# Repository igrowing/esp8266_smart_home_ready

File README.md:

# ESP8266 based Smart Home System
## Principle
### Types of smart home
- Centralized - there is one smart hub in the house and bunch of perfieral devices just perform its commands.
- Decentralized - every edge device is smart and self-contained.
- Cloud - the same as centralized, just the hub is not in your house... with all pros and cons.
- Hybrid - every edge device is smart enough to perform on its own, plus it communicates with the hub in your house or in cloud when/if needed.

We develop the **Hybrid Smart Home**, as the most resilient, safe, and serviceable system.

### What is Smart?

Today every relay connected to Bluetooth called "smart". De facto, this type of "smart" is actually "controlled" device. It is controlled by humans via phone/app/cloud/vocal assistant. So human is smart in this case, not the device.

Smart home consists devices (edge peripherals, hub(s), and cloud connection) which are able to learn habitants behavior, preferences, rules, and perform accordingly to them automatically.

**Smart home must serve people**, not people should care about smart home.

The main concept of our smart home is:
### Home must serve you. You should enjoy ###

This is what this project about.

## Active parts
- [Room sensor](https://github.com/igrowing/esp8266_smart_home_ready/tree/master/modules/room_sensor) based on ESP-easy.
- [Room sensor](https://github.com/igrowing/esp8266_smart_home_ready/tree/master/modules/room%20sensor%20v2) based on Homie IoT.
- [Leakage detector, door/window sensor, remote bell button, etc.](https://github.com/igrowing/esp8266_smart_home_ready/tree/master/modules/leakage_detector) based on ESP-easy.
- [Remote light switch](https://github.com/igrowing/esp8266_smart_home_ready/tree/master/modules/remote%20light%20switch) based on Homie IoT.
- [Sewage pump controller](https://github.com/igrowing/esp8266_smart_home_ready/tree/master/modules/sewage%20pump%20controller) based on Homie IoT.
- [Garden sensor](https://github.com/igrowing/esp8266_smart_home_ready/tree/master/modules/garden_sensor) based on ESP-easy.
- [Water monitor and valve, Schieber](https://github.com/igrowing/esp8266_smart_home_ready/tree/master/modules/schieber) based on Homie IoT.
- [Boilero: the really smart boiler](https://github.com/igrowing/esp8266_smart_home_ready/tree/master/modules/boilero) based on Homie IoT.

## Abandoned part

Spanish proverb says: "Wise man changes his mind, a fool never".
We admit that struggling over the same problems as other developers is not effective way for progress.
Therefore we picked 2 the most usable frameworks (EspEasy and Homie) to implement ESP8266 based part of the smart home.

This impacts a little the fully autonomous OTA idea.
However, this allows us to move faster to end-to-end solution.

## The goal
Make fully automated OTA for ESP8266 under NodeMCU.

The software upload and update to the ESP8266 is trivial via UART. This way is not applicable for mass-deployed modules.

There are geek-driven solutions for OTA: the human (engineer or skilled person) should initiate file upload one-by-one to every particular module. This is not applicable too: the human is unable to do that for hundreds and thousands of modules, tens of files per module.

Therefore, module should initiate itself on the server (register) and request updates on periodic basis. Once developer releases the update to the server, every single ESP8266 module should update itself asynchronously.

### Implementation
**ESP8266 side:** Lua files to be uploaded to the module during "manufacturing" process.

**Server side:** The server files to be installed (copied) to the local server during initial installation process.

## Initial configuration and use
On the server run `smart-home-server.py file_repository`.

The ESP8266 module once powered up will run as AP (access point named SHMxxxxxx, where x-es stand for ID number of the module). Connect ot the module via any browser to address 192.168.4.1. Fill mandatory (and optional if needed) fields. Click Save button. That's it.

The ESP8266 module will restart and connect the server looking for the update. Once new files placed into the file repository the module will download them and run the code.

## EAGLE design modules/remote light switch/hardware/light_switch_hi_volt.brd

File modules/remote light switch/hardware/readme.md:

Schematics in both Eagle SCH and PDF formats.
Board in Eagle BRD format.

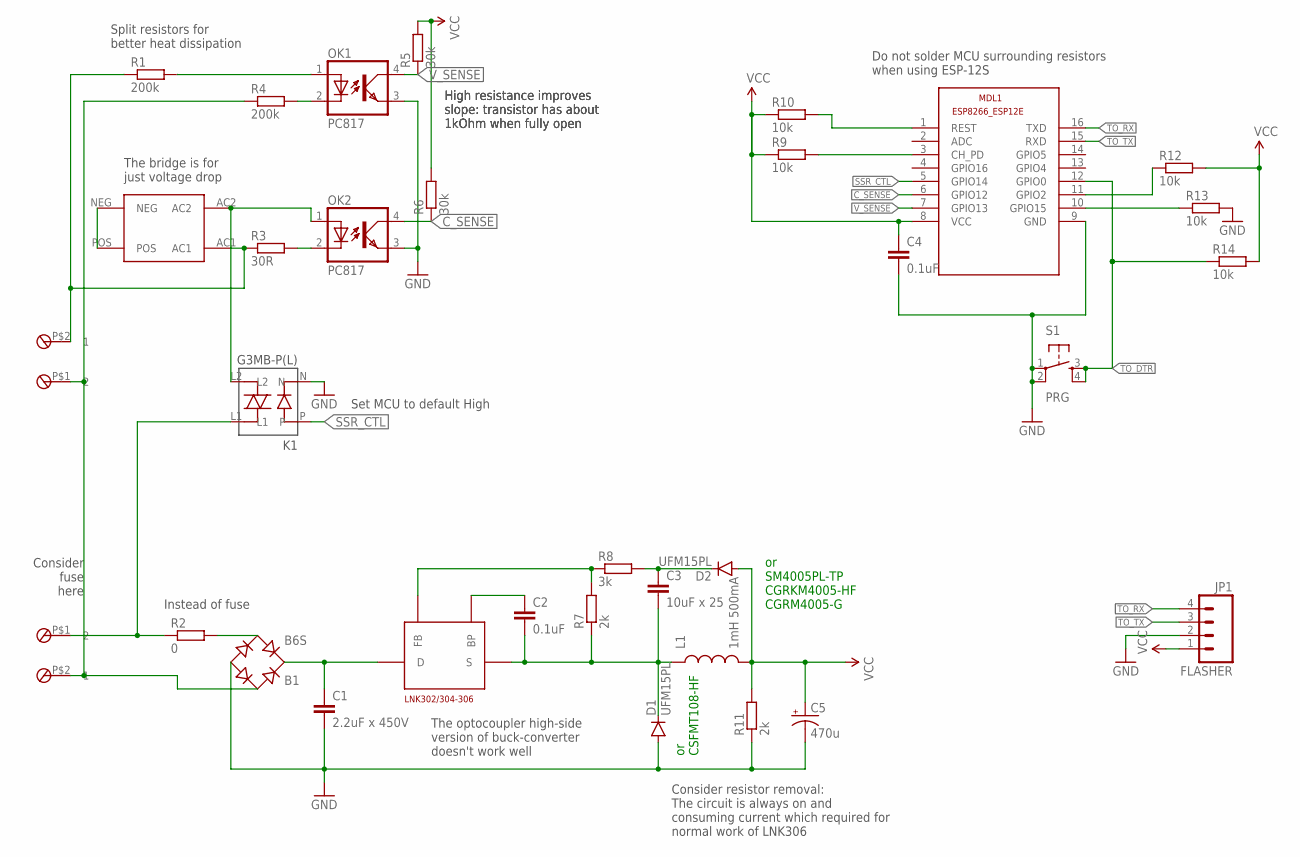
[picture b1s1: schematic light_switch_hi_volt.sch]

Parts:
B1: B6S; MBS
C1: 2.2uF x 450V; C2220K; MPN CKG57NX7T2W225M500JH
C2, C4: 0.1uF; 0805; MPN TMK107BJ104KA-T
C3: 10uF x 25; 0805; MPN GRM219R61E106KA12D
C5: 470u; EIA7343
D1, D2: UFM15PL; SOD-123; MPN UFM15PL-TP
J1, J2: 2POS_TERM_BLK_10A_3.5MM
JP1: FLASHER; 1X04
K1: G3MB-P(L); GB3M_SSR
L1: 1mH 500mA; CDRH125; MPN 46105C
MDL1: ESP8266-12EESP8266-ESP12E; ESP8266-ESP12E
OK1, OK2: PC817; SMD4
R1, R4: 200k; R0805; MPN CRCW06032K00FKEA
R2: 0; R0603; MPN CRCW06032K00FKEA
R3: 30R; R0603; MPN CRCW06032K00FKEA
R5, R6: 30k; R0603; MPN CRCW06032K00FKEA
R7, R11: 2k; R0603; MPN CRCW06032K00FKEA
R8: 3k; R0603; MPN CRCW06032K00FKEA
R9, R10, R12, R13, R14: 10k; R0603
S1: PRG; TACTILE-SWITCH-SMD
U1: Z4DGP406L-HF
U2: LNK306; SO08

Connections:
C_SENSE: MDL1.6 (GPIO12), OK2.4 (COL), R6.1
GND: B1.-, C1.2, C4.2, C5.C (-), D1.A, JP1.2, K1.N, MDL1.9 (GND), OK1.3 (EMIT), OK2.3 (EMIT), R11.1, R13.2, S1.1, S1.2
IO2: MDL1.11 (GPIO2), R12.1
IO15: MDL1.10 (GPIO15), R13.1
unnamed: B1.+, C1.1, U2.4 (D)
unnamed: J2.P$1 (2), K1.L1, R2.1
unnamed: OK1.1 (A), R1.2
unnamed: B1.AC1, J1.P$1 (2), J2.P$2 (1), R4.1
unnamed: U1.NEG, U1.POS
unnamed: B1.AC2, R2.2
unnamed: K1.L2, OK2.1 (A), U1.AC2
unnamed: J1.P$2 (1), R1.1, R3.1, U1.AC1
unnamed: OK2.2 (C), R3.2
unnamed: OK1.2 (C), R4.2
unnamed: MDL1.3 (CH_PD), R9.2
unnamed: C2.1, U2.1 (BP)
unnamed: C2.2, C3.2, D1.C, L1.1, R7.1, U2.5 (S), U2.6 (S), U2.7 (S), U2.8 (S)
unnamed: R7.2, R8.1, U2.2 (FB)
unnamed: C3.1, D2.C, R8.2
SSR_CTL: K1.P, MDL1.5 (GPIO14)
TO_DTR: MDL1.12 (GPIO0), R14.1, S1.3, S1.4
TO_RTS: MDL1.1 (REST), R10.2
TO_RX: JP1.4, MDL1.16 (TXD)
TO_TX: JP1.3, MDL1.15 (RXD)
VCC: C4.1, C5.A (+), D2.A, JP1.1, L1.2, MDL1.8 (VCC), R5.2, R6.2, R9.1, R10.1, R11.2, R12.2, R14.2
V_SENSE: MDL1.7 (GPIO13), OK1.4 (COL), R5.1

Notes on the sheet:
or CSFMT108-HF
or SM4005PL-TP CGRKM4005-HF CGRM4005-G
Split resistors for better heat dissipation
High resistance improves slope: transistor has about 1kOhm when fully open
The bridge is for just voltage drop
Consider resistor removal: The circuit is always on and consuming current which required for normal work of LNK306
The optocoupler high-side version of buck-converter doesn't work well
Instead of fuse
Do not solder MCU surrounding resistors when using ESP-12S
Set MCU to default High
Consider fuse here

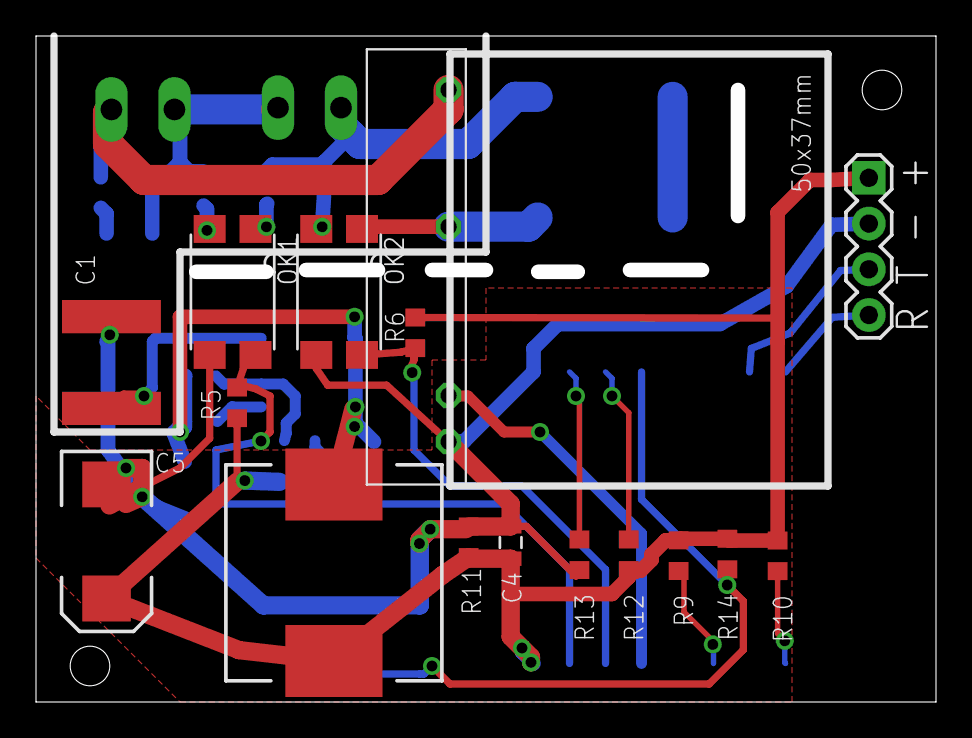
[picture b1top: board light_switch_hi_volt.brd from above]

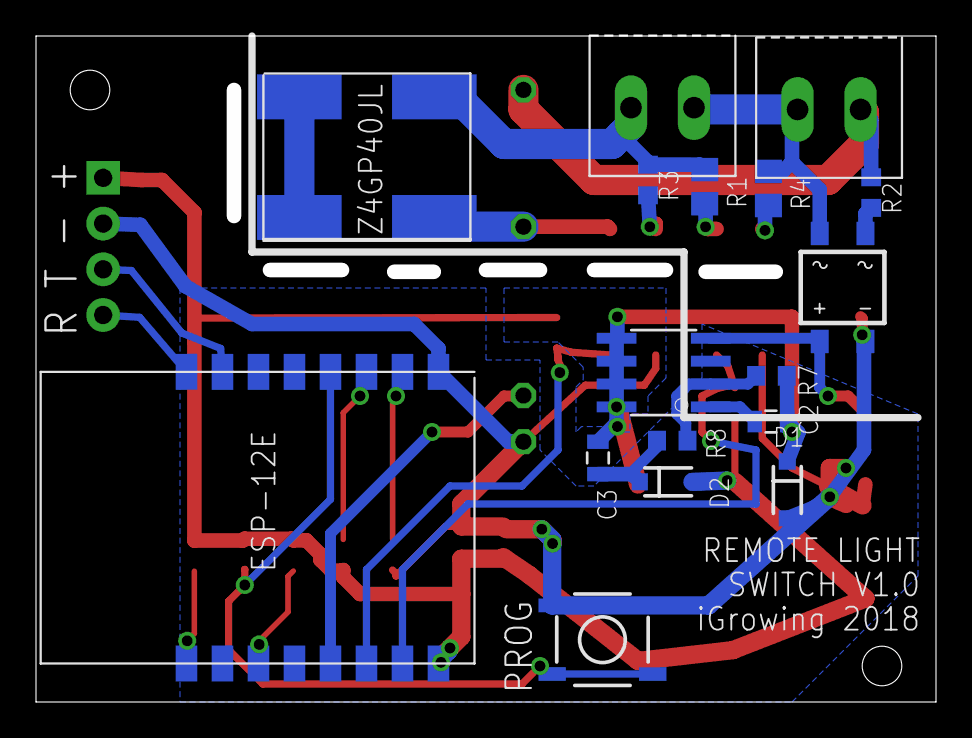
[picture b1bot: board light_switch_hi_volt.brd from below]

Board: 2 copper layers, 49.2 x 36.2 mm, 33 parts (17 on the bottom side), 26 nets.

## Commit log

2018-03-25 Create readme.md
    Initial commit
2018-03-25 Update readme.md
    alternatives added
2018-03-25 Update readme.md
    todos
2018-03-31 Schematics and rules
2018-03-31 Instructions added
2018-03-31 init.rev
2018-03-31 Config.dat added
2018-03-31 instructions improved.
2018-03-31 Instructions added.
2018-03-31 Project content added
2018-07-16 BME680 recommended
2018-07-16 init.rev.
2018-07-16 formatting
2018-07-16 uploaded files.
2018-11-02 Files added.
2018-11-02 ini file
2018-11-02 Create placeholder
2018-11-02 the sketch
2018-11-04 Noise immunity
2018-11-04 Keep/restore last state, Noise immunity
2018-11-04 Description
2018-12-08 ini files added
2018-12-08 typos
2018-12-16 Schematics
2018-12-16 Init.publish.
2018-12-16 LAF improved
2018-12-16 Node-RED flow for UI of the pump controller
2018-12-16 pictures
2018-12-16 pictures added
2018-12-16 Rename nr_flow.js to nr_flow.json
2018-12-19 install mode added
2018-12-19 Improved current/distance measure, alerting, install mode added.
2018-12-19 Improved stability and protection.
2018-12-28 Allow scheduler on/off via MQTT
    New event added due to inability of EspEasy to use taskvalueset command directly from MQTT
2018-12-28 Fix NTP server reference
2018-12-28 Usage added.
2019-01-19 Complete leakage procedure with deepsleep
    Powering off the unit on leakage doesn't work. The unit awakes up immediately. Deepsleep makes awake slow. Power cycle the unit to exit the deepsleep cycle.
2019-01-19 Usage added
2019-02-16 Debugged distance meter
2019-02-16 Pictures seen now.
2019-03-11 Adapted for compilation for 4MB flash
2019-03-11 Bugfix: avoid false alerts about relay state
2019-03-11 STL box model for 3D printer
2019-03-22 Don't retain MQTT messages
2019-03-22 Improved controller online/offline detection
2019-03-22 Node-RED flow example added
2019-03-31 Added air quality calculation and reporting
2019-04-04 Added verbal weather forecast reporting
2019-04-04 Node-Red integration example
2019-04-04 Node-Red flow example
2019-04-05 UI screenshot added
2019-04-05 Bug fix in weather forecast. Reorg write to file
2019-04-21 Improve report consistency
2019-07-07 Init. rev.
2019-07-07 Wave added
2019-07-08 performance optimized
2019-07-21 Added usage by MQTT
2019-07-21 How it works added
2019-07-24 Optimized and visually reorg'd
2019-07-24 picture added
2019-07-26 Optimized Flash use and water reporting
2019-07-27 Node-Red flow picture added
2019-07-27 Typo
2019-07-27 Added extrapolation of water flow while Shiber is booting and water isn't counted
2019-07-30 update flow
2019-07-30 Node-Red flow added
2019-08-02 Added periodic report of distance threshold to keep UI updated
2019-08-02 Remove duplicated invocation of 15sec power_timer. Optimization.
2019-08-02 Mount added
2019-08-05 UI usage added
2019-08-09 Hall to Reed upgrade
2019-08-09 Bugfix: report measurement only after all settings restored from Flash
2019-08-11 Added data load to InfluxDB
2019-08-15 Adjust volume calculation by flow speed
2019-08-23 Optimize variable reporting and water flow calculation
2019-08-24 log() -> log10f()
2019-09-11 Optimizations, bugfixes, reorg
2019-09-13 Stuff added
2019-09-14 Minor bugfix
2019-09-17 Avoid flow alerting before flow counters initialized
2020-02-14 Improved EMI, reorg.
2020-02-14 Remove diode to get reliable water reading
2020-02-14 Enable debug
2020-02-16 Soft_delay() instead of delay(). Fix get_liters(). Power off is no wifi in timeout.
2020-03-13 Replace mistaken commit
2020-03-14 schematics added
2020-03-18 Refactoring and bug fixes
2020-03-18 EMI + better PSU
2020-03-20 Make all settings as properties, add feedback to UI
2020-03-20 Replace dedicated PSU with generic USB PSU + LDO
2020-03-20 More docs and pictures
2020-03-20 attempt to fix image size
2020-03-20 Fix picture resizing
2020-03-20 Minor fix
2020-03-23 Logic explained
2020-04-24 Improve calibration in volume calc
2021-01-15 Air pressure correction described
2021-01-16 Added correction with dependency of air pressure
2021-01-16 ini-file added
2021-01-16 platformio.ini update
2021-01-16 Bug fixes
2021-01-23 Bug fix and better corrected time report
2021-02-02 Workaround bug in Ticker library
2021-02-08 Tuning to pressure compensation mechanism.
2021-02-19 readme.md update
2021-03-05 Create temp
2021-03-05 Pictures upload
2021-03-05 Code upload
2021-03-05 readme upload
2021-03-06 More pictures added
2021-03-06 Bug fix in water level representation
2021-03-06 remove it
2021-04-02 2 more buttons added to Web-UI
2021-04-02 Add alert for long no drink timeout
2021-04-02 Readme update
2021-04-17 Improved messaging, Filter hours bug fix
2021-08-06 Bug fix: restart the pet scanning if the pet was thirsty
2021-08-16 Fix link
2021-08-16 Warning!
2022-12-23 Update to work with Maxbotix MB-7062 sonar
2022-12-24 Turn off the sonar while not measuring.
2023-02-16 put placeholder
2023-02-16 Works
2023-02-17 Schematics added.
2023-02-18 Bug fix.
2023-04-19 Set explisit version of espressif8266 lib for stable build
2023-04-19 Display 'SUSPENDED' in 'Next on' when boiler function is suspended

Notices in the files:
parts and their libraries:
SparkFun-Capacitors: Licensing: Creative Commons ShareAlike 4.0 International - https://creativecommons.org/licenses/by-sa/4.0
